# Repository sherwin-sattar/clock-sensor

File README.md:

# Clock-Sensor

## User Interface

Web user interface allows seamless control and customization of a clock display, featuring 86 addressable LEDs. Users can adjust and control the clock’s display from anywhere in the world through a secure online connection.
In addition to clock control, the UI also provides real-time monitoring of environmental conditions, including live temperature and humidity readings. Historical data is visualized through easy-to-read graphs, allowing users to track past temperature and humidity trends.

## 3D views

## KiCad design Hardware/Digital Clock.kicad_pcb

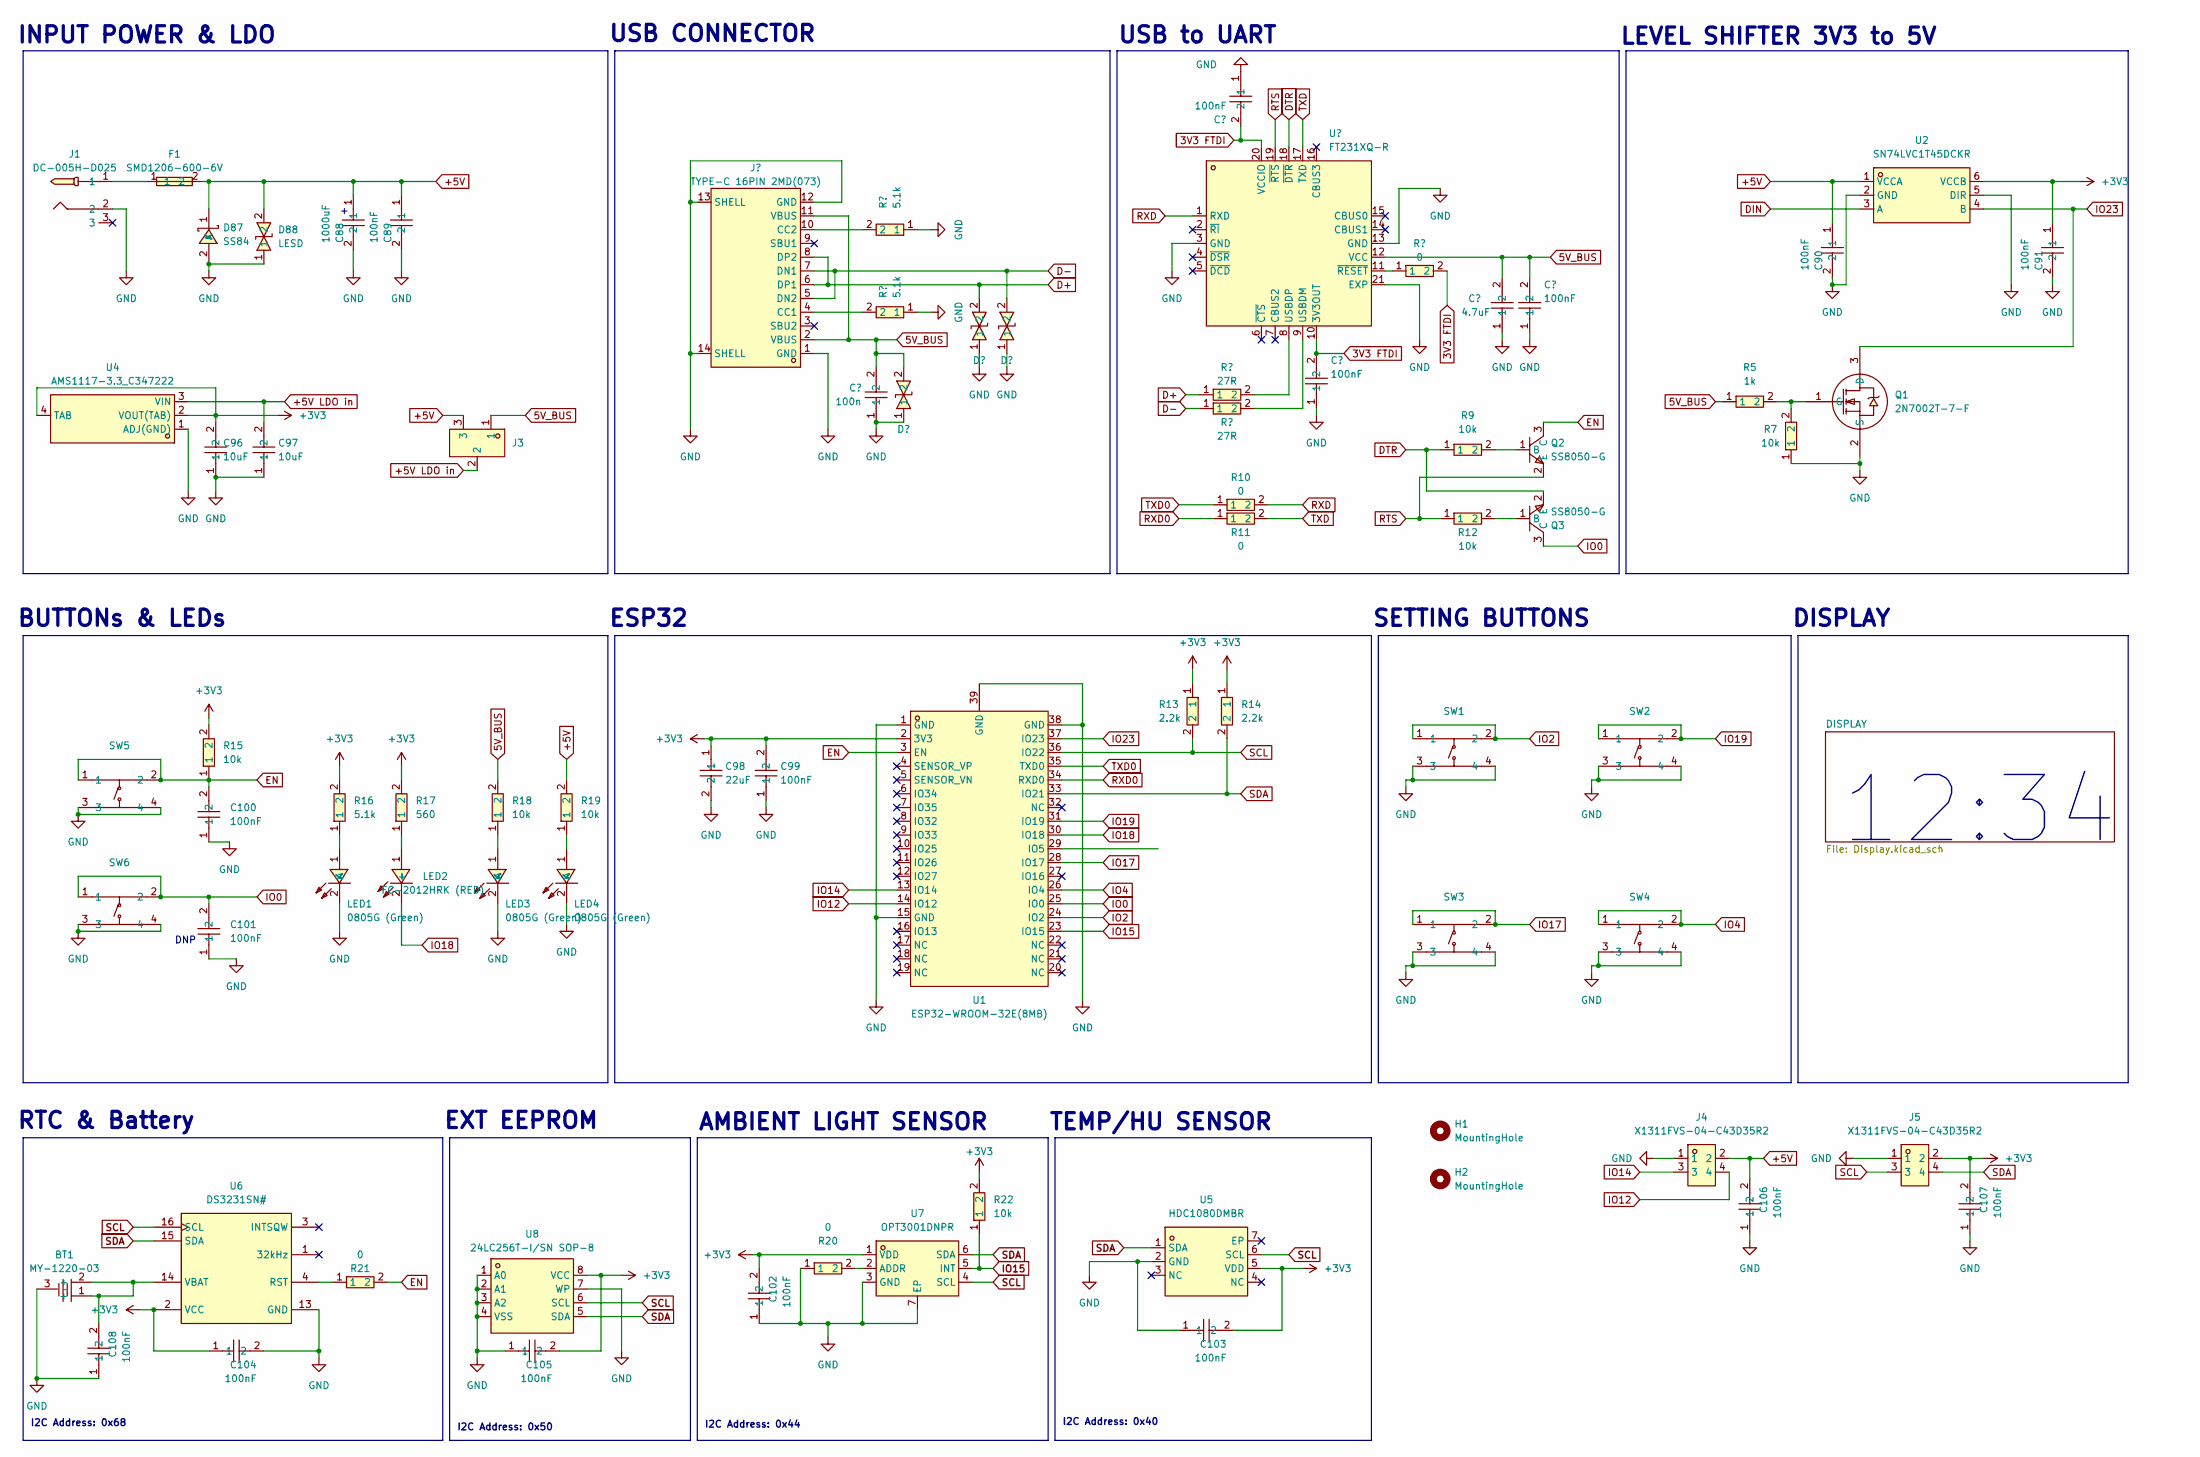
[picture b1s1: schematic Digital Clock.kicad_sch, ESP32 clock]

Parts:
BT1: MY-1220-03; BAT-SMD_MY-1220-03; LCSC Part C964818
C87, C89, C90, C91, C93, C94, C99, C100, C101, C102, C103, C104, C105, C106, C107, C108: 100nF; C0402; LCSC Part C1525
C88: 1000uF; CAP-SMD_BD10.0-L10.3-W10.3-LS11.3-FD; LCSC Part C310843
C92: 4.7uF; C0402; LCSC Part C368809
C95: 100n; C0402; LCSC Part C1525
C96, C97: 10uF; C0402; LCSC Part C315248
C98: 22uF; C0805; LCSC Part C602037
D87: SS84; SMC_L6.9-W5.9-LS7.9-RD; LCSC Part C2943761
D88: LESD; SOD-523_L1.2-W0.8-LS1.6-BI; LCSC Part C383211
D89, D90, D91: SOD-523_L1.2-W0.8-LS1.6-BI; LCSC Part C383211
F1: SMD1206-600-6V; F1206; LCSC Part C2760310
H1, H2: MountingHole; MountingHole_3.7mm_Pad_TopBottom
J1: DC-005H-D025; DC-IN-TH_G-SWITCH_DC-005H-D025; LCSC Part C5353839
J2: TYPE-C 16PIN 2MD(073); USB-C-SMD_TYPE-C-6PIN-2MD-073; LCSC Part C2765186
J3: X1311WVS-03J-C40D42R2; HDR-SMD_3P-P1.27-V-M-LS4.2_X1311WVS-03J-C40D42R2; LCSC Part C5243526
J4, J5: X1311FVS-04-C43D35R2; HDR-SMD_4P-P1.27-V-F-LS4.5_R2; LCSC Part C2881513
LED1, LED3, LED4: 0805G (Green); LED0805-R-RD; LCSC Part C2297
LED2: FC-2012HRK (RED); LED0805-R-RD; LCSC Part C84256
Q1: 2N7002T-7-F; SOT-523-3_L1.6-W0.8-P1.00-LS1.6-BR; LCSC Part C139445
Q2, Q3: SS8050-G; SOT-23-3_L2.9-W1.3-P1.90-LS2.4-BR; LCSC Part C164886
R2, R4, R16: 5.1k; R0402; LCSC Part C25905
R3, R10, R11, R20, R21: 0; R0402; LCSC Part C17168
R5: 1k; R0402; LCSC Part C11702
R6, R8: 27R; R0402; LCSC Part C138021
R7, R9, R12, R15, R18, R19, R22: 10k; R0402; LCSC Part C25744
R13, R14: 2.2k; R0402; LCSC Part C25879
R17: 560; R0402; LCSC Part C25126
SW1, SW2, SW3, SW4, SW5, SW6: PTS645SH50SMTR92LFS; KEY-SMD_4P-L6.0-W6.0-P4.50-LS9.0; LCSC Part C221869
U1: ESP32-WROOM-32E(8MB); WIFI-SMD_ESP32-WROOM-32E; LCSC Part C701342
U2: SN74LVC1T45DCKR; SC-70-6_L2.2-W1.3-P0.65-LS2.2-BR; LCSC Part C9382
U3: FT231XQ-R; QFN-20_L4.0-W4.0-P0.50-BL-EP2.2; LCSC Part C132159
U4: AMS1117-3.3_C347222; SOT-223-4_L6.5-W3.5-P2.30-LS7.0-BR; LCSC Part C347222
U5: HDC1080DMBR; SENSOR-SMD_HDC1080DMBR; LCSC Part C82227
U6: DS3231SN#; SOIC-16_L10.3-W7.5-P1.27-LS10.3-BL; LCSC Part C9866
U7: OPT3001DNPR; USON6_L2.1-W2.1-P0.65-BL-EP; LCSC Part C90462
U8: 24LC256T-I/SN SOP-8; SOIC-8_L4.9-W3.9-P1.27-LS6.0-BL; LCSC Part C5458

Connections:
3V3 FTDI: C87.2, C94.2, R3.2, U3.10 (3V3OUT), U3.20 (VCCIO)
5V_BUS: C92.2, C93.2, C95.2, D91.2, J2.2 (VBUS), J2.11 (VBUS), J3.1, R5.1, R18.2, U3.12 (VCC)
+3V3: C91.1, C96.2, C98.1, C99.2, C102.2, C103.2, C104.1, C105.2, C107.2, J5.2, R13.1, R14.1, R15.2, R16.2, R17.2, R22.2, U1.2 (3V3), U2.6 (VCCB), U4.2 (VOUT(TAB)), U4.4 (TAB), U5.5 (VDD), U6.2 (VCC), U7.1 (VDD), U8.8 (VCC)
+5V: C88.1, C89.1, C90.1, C106.2, D87.1 (K), D88.2, F1.2, J3.3, J4.2, R19.2, U2.1 (VCCA); also elsewhere on the board
+5V LDO in: C97.2, J3.2, U4.3 (VIN)
D+: D89.2, J2.6 (DP1), J2.8 (DP2), R6.1
D-: D90.2, J2.5 (DN2), J2.7 (DN1), R8.1
DIN: U2.3 (A); also elsewhere on the board
DTR: Q3.2 (E), R9.1, U3.18 (~DTR)
EN: C100.2, Q2.3 (C), R15.1, R21.2, SW5.1, SW5.2, U1.3 (EN)
GND: BT1.3 (-), C87.1, C88.2, C89.2, C90.2, C91.2, C92.1, C93.1, C94.1, C95.1, C96.1, C97.1, C98.2, C99.1, C100.1, C101.1, C102.1, C103.1, C104.2, C105.1, C106.1, C107.1, C108.1, D87.2 (A), D88.1, D89.1, D90.1, D91.1, J1.2, J2.1 (GND), J2.12 (GND), J2.13 (SHELL), J2.14 (SHELL), J4.1, J5.1, LED1.2 (K), LED3.2 (K), LED4.2 (K), Q1.2 (S), R2.1, R4.1, R7.1, R20.1, SW1.3, SW1.4, SW2.3, SW2.4, SW3.3, SW3.4, SW4.3, SW4.4, SW5.3, SW5.4, SW6.3, SW6.4, U1.1 (GND), U1.15 (GND), U1.38 (GND), U1.39 (GND), U2.2 (GND), U2.5 (DIR), U3.3 (GND), U3.13 (GND), U3.21 (EXP), U4.1 (ADJ(GND)), U5.2 (GND), U6.13 (GND), U7.3 (GND), U7.7 (EP), U8.1 (A0), U8.2 (A1), U8.3 (A2), U8.4 (VSS), U8.7 (WP); also elsewhere on the board
IO0: C101.2, Q3.3 (C), SW6.1, SW6.2, U1.25 (IO0)
IO2: SW1.1, SW1.2, U1.24 (IO2)
IO4: SW4.1, SW4.2, U1.26 (IO4)
IO12: J4.4, U1.14 (IO12)
IO14: J4.3, U1.13 (IO14)
IO15: R22.1, U1.23 (IO15), U7.5 (INT)
IO17: SW3.1, SW3.2, U1.28 (IO17)
IO18: LED2.2 (-), U1.30 (IO18); also elsewhere on the board
IO19: SW2.1, SW2.2, U1.31 (IO19)
IO23: Q1.3 (D), U1.37 (IO23), U2.4 (B)
unnamed: F1.1, J1.1
unnamed: J2.4 (CC1), R4.2
unnamed: J2.10 (CC2), R2.2
unnamed 102: LED1.1 (A), R16.1; also elsewhere on the board
unnamed 103: LED2.1 (+), R17.1; also elsewhere on the board
unnamed 104: LED3.1 (A), R18.1; also elsewhere on the board
unnamed 105: LED4.1 (A), R19.1; also elsewhere on the board
unnamed: Q1.1 (G), R5.2, R7.2
unnamed: Q2.1 (B), R9.2
unnamed: Q3.1 (B), R12.2
unnamed: R8.2, U3.9 (USBDM)
unnamed: R6.2, U3.8 (USBDP)
unnamed: R3.1, U3.11 (~RESET)
unnamed: R21.1, U6.4 (RST)
unnamed: BT1.1 (+), BT1.2 (+), C108.2, U6.14 (VBAT)
unnamed: R20.2, U7.2 (ADDR)
RTS: Q2.2 (E), R12.1, U3.19 (~RTS)
RXD: R10.2, U3.1 (RXD)
RXD0: R11.1, U1.34 (RXD0)
SCL: J5.3, R13.2, U1.36 (IO22), U5.6 (SCL), U6.16 (SCL), U7.4 (SCL), U8.6 (SCL)
SDA: J5.4, R14.2, U1.33 (IO21), U5.1 (SDA), U6.15 (SDA), U7.6 (SDA), U8.5 (SDA)
TXD: R11.2, U3.17 (TXD)
TXD0: R10.1, U1.35 (TXD0)

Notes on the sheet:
I2C Address: 0x44
INPUT POWER & LDO
USB CONNECTOR
BUTTONs & LEDs
USB to UART
ESP32
RTC & Battery
I2C Address: 0x68
EXT EEPROM
AMBIENT LIGHT SENSOR
I2C Address: 0x50
I2C Address: 0x40
DNP
TEMP/HU SENSOR
12:34
LEVEL SHIFTER 3V3 to 5V
SETTING BUTTONS
DISPLAY

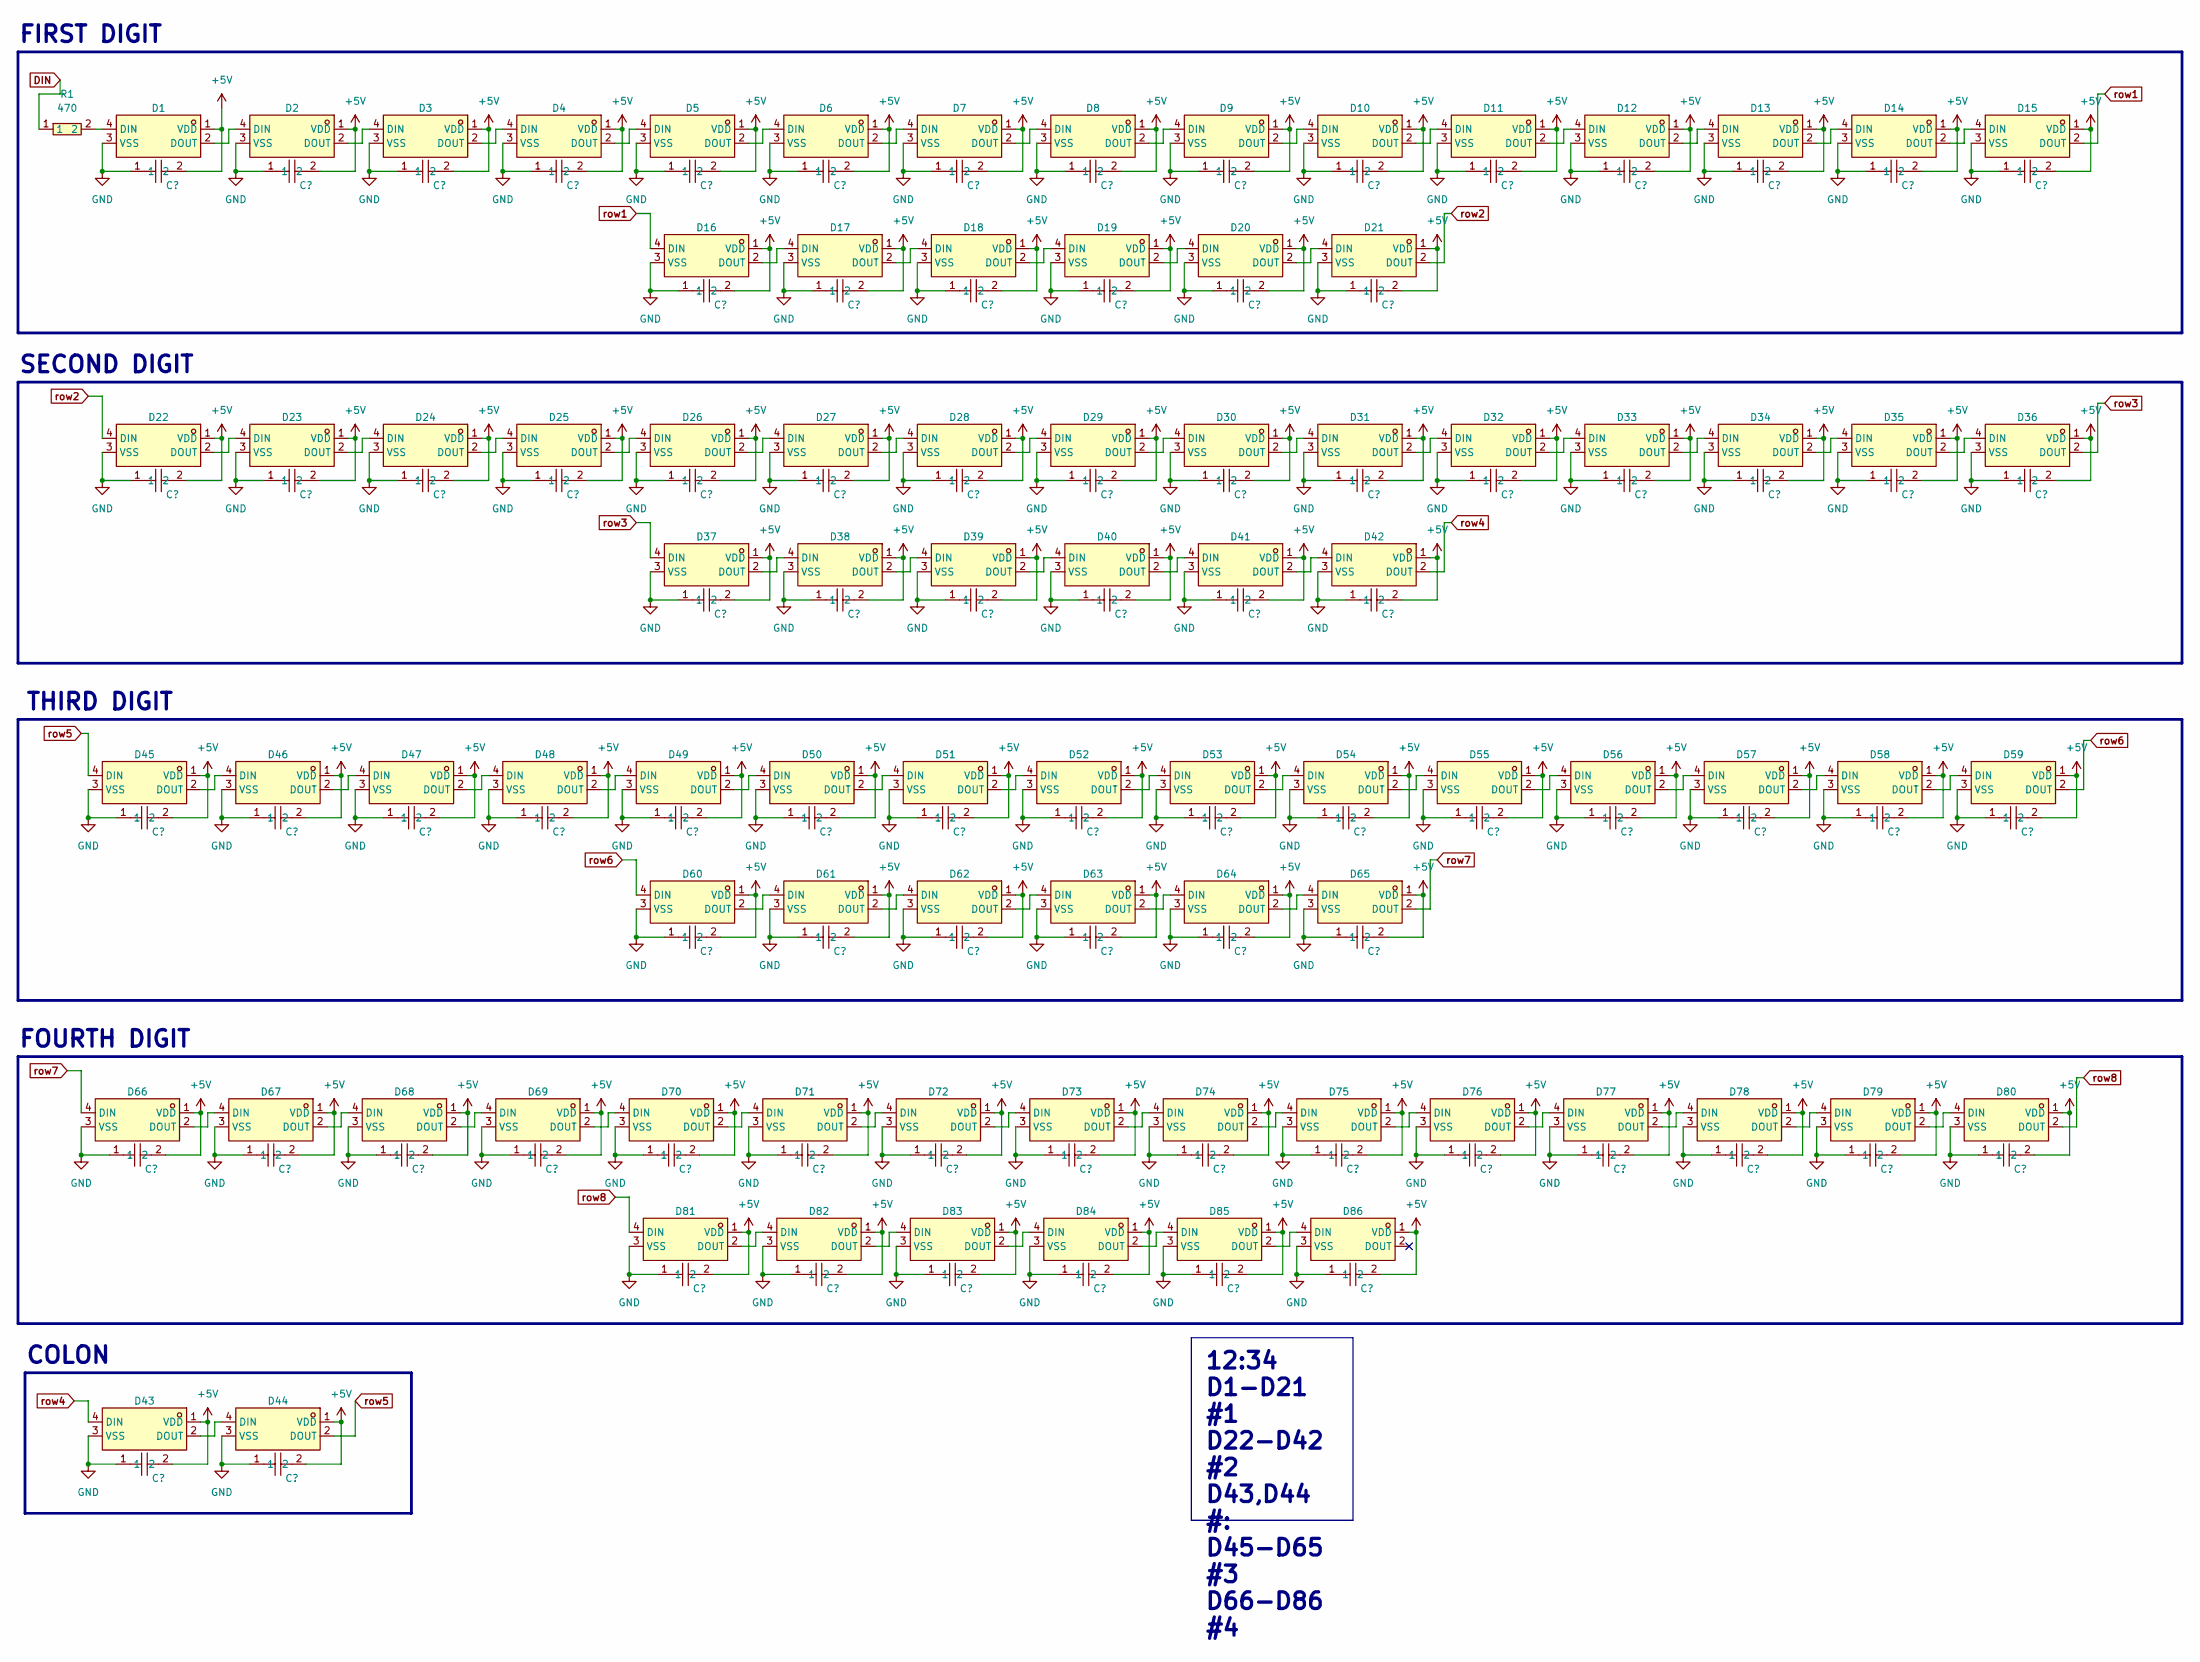
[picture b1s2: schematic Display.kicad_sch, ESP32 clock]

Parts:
C1, C2, C3, C4, C5, C6, C7, C8, C9, C10, C11, C12, C13, C14, C15, C16, C17, C18, C19, C20, C21, C22, C23, C24, C25, C26, C27, C28, C29, C30, C31, C32, C33, C34, C35, C36, C37, C38, C39, C40, C41, C42, C43, C44, C45, C46, C47, C48, C49, C50, C51, C52, C53, C54, C55, C56, C57, C58, C59, C60, C61, C62, C63, C64, C65, C66, C67, C68, C69, C70, C71, C72, C73, C74, C75, C76, C77, C78, C79, C80, C81, C82, C83, C84, C85, C86: 100nF; C0402; LCSC Part C1525
D1, D2, D3, D4, D5, D6, D7, D8, D9, D10, D11, D12, D13, D14, D15, D16, D17, D18, D19, D20, D21, D22, D23, D24, D25, D26, D27, D28, D29, D30, D31, D32, D33, D34, D35, D36, D37, D38, D39, D40, D41, D42, D43, D44, D45, D46, D47, D48, D49, D50, D51, D52, D53, D54, D55, D56, D57, D58, D59, D60, D61, D62, D63, D64, D65, D66, D67, D68, D69, D70, D71, D72, D73, D74, D75, D76, D77, D78, D79, D80, D81, D82, D83, D84, D85, D86: WS2812B-MINI; LED-SMD_4P-L3.5-W3.5-TL_WS2812B; LCSC Part C527089
R1: 470; R0402; LCSC Part C25117

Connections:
+5V: C1.2, C2.2, C3.2, C4.2, C5.2, C6.2, C7.2, C8.2, C9.2, C10.2, C11.2, C12.2, C13.2, C14.2, C15.2, C16.2, C17.2, C18.2, C19.2, C20.2, C21.2, C22.2, C23.2, C24.2, C25.2, C26.2, C27.2, C28.2, C29.2, C30.2, C31.2, C32.2, C33.2, C34.2, C35.2, C36.2, C37.2, C38.2, C39.2, C40.2, C41.2, C42.2, C43.2, C44.2, C45.2, C46.2, C47.2, C48.2, C49.2, C50.2, C51.2, C52.2, C53.2, C54.2, C55.2, C56.2, C57.2, C58.2, C59.2, C60.2, C61.2, C62.2, C63.2, C64.2, C65.2, C66.2, C67.2, C68.2, C69.2, C70.2, C71.2, C72.2, C73.2, C74.2, C75.2, C76.2, C77.2, C78.2, C79.2, C80.2, C81.2, C82.2, C83.2, C84.2, C85.2, C86.2, D1.1 (VDD), D2.1 (VDD), D3.1 (VDD), D4.1 (VDD), D5.1 (VDD), D6.1 (VDD), D7.1 (VDD), D8.1 (VDD), D9.1 (VDD), D10.1 (VDD), D11.1 (VDD), D12.1 (VDD), D13.1 (VDD), D14.1 (VDD), D15.1 (VDD), D16.1 (VDD), D17.1 (VDD), D18.1 (VDD), D19.1 (VDD), D20.1 (VDD), D21.1 (VDD), D22.1 (VDD), D23.1 (VDD), D24.1 (VDD), D25.1 (VDD), D26.1 (VDD), D27.1 (VDD), D28.1 (VDD), D29.1 (VDD), D30.1 (VDD), D31.1 (VDD), D32.1 (VDD), D33.1 (VDD), D34.1 (VDD), D35.1 (VDD), D36.1 (VDD), D37.1 (VDD), D38.1 (VDD), D39.1 (VDD), D40.1 (VDD), D41.1 (VDD), D42.1 (VDD), D43.1 (VDD), D44.1 (VDD), D45.1 (VDD), D46.1 (VDD), D47.1 (VDD), D48.1 (VDD), D49.1 (VDD), D50.1 (VDD), D51.1 (VDD), D52.1 (VDD), D53.1 (VDD), D54.1 (VDD), D55.1 (VDD), D56.1 (VDD), D57.1 (VDD), D58.1 (VDD), D59.1 (VDD), D60.1 (VDD), D61.1 (VDD), D62.1 (VDD), D63.1 (VDD), D64.1 (VDD), D65.1 (VDD), D66.1 (VDD), D67.1 (VDD), D68.1 (VDD), D69.1 (VDD), D70.1 (VDD), D71.1 (VDD), D72.1 (VDD), D73.1 (VDD), D74.1 (VDD), D75.1 (VDD), D76.1 (VDD), D77.1 (VDD), D78.1 (VDD), D79.1 (VDD), D80.1 (VDD), D81.1 (VDD), D82.1 (VDD), D83.1 (VDD), D84.1 (VDD), D85.1 (VDD), D86.1 (VDD); also elsewhere on the board
DIN: R1.1; also elsewhere on the board
GND: C1.1, C2.1, C3.1, C4.1, C5.1, C6.1, C7.1, C8.1, C9.1, C10.1, C11.1, C12.1, C13.1, C14.1, C15.1, C16.1, C17.1, C18.1, C19.1, C20.1, C21.1, C22.1, C23.1, C24.1, C25.1, C26.1, C27.1, C28.1, C29.1, C30.1, C31.1, C32.1, C33.1, C34.1, C35.1, C36.1, C37.1, C38.1, C39.1, C40.1, C41.1, C42.1, C43.1, C44.1, C45.1, C46.1, C47.1, C48.1, C49.1, C50.1, C51.1, C52.1, C53.1, C54.1, C55.1, C56.1, C57.1, C58.1, C59.1, C60.1, C61.1, C62.1, C63.1, C64.1, C65.1, C66.1, C67.1, C68.1, C69.1, C70.1, C71.1, C72.1, C73.1, C74.1, C75.1, C76.1, C77.1, C78.1, C79.1, C80.1, C81.1, C82.1, C83.1, C84.1, C85.1, C86.1, D1.3 (VSS), D2.3 (VSS), D3.3 (VSS), D4.3 (VSS), D5.3 (VSS), D6.3 (VSS), D7.3 (VSS), D8.3 (VSS), D9.3 (VSS), D10.3 (VSS), D11.3 (VSS), D12.3 (VSS), D13.3 (VSS), D14.3 (VSS), D15.3 (VSS), D16.3 (VSS), D17.3 (VSS), D18.3 (VSS), D19.3 (VSS), D20.3 (VSS), D21.3 (VSS), D22.3 (VSS), D23.3 (VSS), D24.3 (VSS), D25.3 (VSS), D26.3 (VSS), D27.3 (VSS), D28.3 (VSS), D29.3 (VSS), D30.3 (VSS), D31.3 (VSS), D32.3 (VSS), D33.3 (VSS), D34.3 (VSS), D35.3 (VSS), D36.3 (VSS), D37.3 (VSS), D38.3 (VSS), D39.3 (VSS), D40.3 (VSS), D41.3 (VSS), D42.3 (VSS), D43.3 (VSS), D44.3 (VSS), D45.3 (VSS), D46.3 (VSS), D47.3 (VSS), D48.3 (VSS), D49.3 (VSS), D50.3 (VSS), D51.3 (VSS), D52.3 (VSS), D53.3 (VSS), D54.3 (VSS), D55.3 (VSS), D56.3 (VSS), D57.3 (VSS), D58.3 (VSS), D59.3 (VSS), D60.3 (VSS), D61.3 (VSS), D62.3 (VSS), D63.3 (VSS), D64.3 (VSS), D65.3 (VSS), D66.3 (VSS), D67.3 (VSS), D68.3 (VSS), D69.3 (VSS), D70.3 (VSS), D71.3 (VSS), D72.3 (VSS), D73.3 (VSS), D74.3 (VSS), D75.3 (VSS), D76.3 (VSS), D77.3 (VSS), D78.3 (VSS), D79.3 (VSS), D80.3 (VSS), D81.3 (VSS), D82.3 (VSS), D83.3 (VSS), D84.3 (VSS), D85.3 (VSS), D86.3 (VSS); also elsewhere on the board
unnamed: D1.4 (DIN), R1.2
unnamed: D1.2 (DOUT), D2.4 (DIN)
unnamed: D2.2 (DOUT), D3.4 (DIN)
unnamed: D3.2 (DOUT), D4.4 (DIN)
unnamed: D4.2 (DOUT), D5.4 (DIN)
unnamed: D5.2 (DOUT), D6.4 (DIN)
unnamed: D6.2 (DOUT), D7.4 (DIN)
unnamed: D7.2 (DOUT), D8.4 (DIN)
unnamed: D8.2 (DOUT), D9.4 (DIN)
unnamed: D9.2 (DOUT), D10.4 (DIN)
unnamed: D10.2 (DOUT), D11.4 (DIN)
unnamed: D11.2 (DOUT), D12.4 (DIN)
unnamed: D12.2 (DOUT), D13.4 (DIN)
unnamed: D13.2 (DOUT), D14.4 (DIN)
unnamed: D14.2 (DOUT), D15.4 (DIN)
unnamed: D16.2 (DOUT), D17.4 (DIN)
unnamed: D17.2 (DOUT), D18.4 (DIN)
unnamed: D18.2 (DOUT), D19.4 (DIN)
unnamed: D19.2 (DOUT), D20.4 (DIN)
unnamed: D20.2 (DOUT), D21.4 (DIN)
unnamed: D22.2 (DOUT), D23.4 (DIN)
unnamed: D23.2 (DOUT), D24.4 (DIN)
unnamed: D24.2 (DOUT), D25.4 (DIN)
unnamed: D25.2 (DOUT), D26.4 (DIN)
unnamed: D26.2 (DOUT), D27.4 (DIN)
unnamed: D27.2 (DOUT), D28.4 (DIN)
unnamed: D28.2 (DOUT), D29.4 (DIN)
unnamed: D29.2 (DOUT), D30.4 (DIN)
unnamed: D30.2 (DOUT), D31.4 (DIN)
unnamed: D31.2 (DOUT), D32.4 (DIN)
unnamed: D32.2 (DOUT), D33.4 (DIN)
unnamed: D33.2 (DOUT), D34.4 (DIN)
unnamed: D34.2 (DOUT), D35.4 (DIN)
unnamed: D35.2 (DOUT), D36.4 (DIN)
unnamed: D37.2 (DOUT), D38.4 (DIN)
unnamed: D38.2 (DOUT), D39.4 (DIN)
unnamed: D39.2 (DOUT), D40.4 (DIN)
unnamed: D40.2 (DOUT), D41.4 (DIN)
unnamed: D41.2 (DOUT), D42.4 (DIN)
unnamed: D43.2 (DOUT), D44.4 (DIN)
unnamed: D45.2 (DOUT), D46.4 (DIN)
unnamed: D46.2 (DOUT), D47.4 (DIN)
unnamed: D47.2 (DOUT), D48.4 (DIN)
unnamed: D48.2 (DOUT), D49.4 (DIN)
unnamed: D49.2 (DOUT), D50.4 (DIN)
unnamed: D50.2 (DOUT), D51.4 (DIN)
unnamed: D51.2 (DOUT), D52.4 (DIN)
unnamed: D52.2 (DOUT), D53.4 (DIN)
unnamed: D53.2 (DOUT), D54.4 (DIN)
unnamed: D54.2 (DOUT), D55.4 (DIN)
unnamed: D55.2 (DOUT), D56.4 (DIN)
unnamed: D56.2 (DOUT), D57.4 (DIN)
unnamed: D57.2 (DOUT), D58.4 (DIN)
unnamed: D58.2 (DOUT), D59.4 (DIN)
unnamed: D60.2 (DOUT), D61.4 (DIN)
unnamed: D61.2 (DOUT), D62.4 (DIN)
unnamed: D62.2 (DOUT), D63.4 (DIN)
unnamed: D63.2 (DOUT), D64.4 (DIN)
unnamed: D64.2 (DOUT), D65.4 (DIN)
unnamed: D66.2 (DOUT), D67.4 (DIN)
unnamed: D67.2 (DOUT), D68.4 (DIN)
unnamed: D68.2 (DOUT), D69.4 (DIN)
unnamed: D69.2 (DOUT), D70.4 (DIN)
unnamed: D70.2 (DOUT), D71.4 (DIN)
unnamed: D71.2 (DOUT), D72.4 (DIN)
unnamed: D72.2 (DOUT), D73.4 (DIN)
unnamed: D73.2 (DOUT), D74.4 (DIN)
unnamed: D74.2 (DOUT), D75.4 (DIN)
unnamed: D75.2 (DOUT), D76.4 (DIN)
unnamed: D76.2 (DOUT), D77.4 (DIN)
unnamed: D77.2 (DOUT), D78.4 (DIN)
unnamed: D78.2 (DOUT), D79.4 (DIN)
unnamed: D79.2 (DOUT), D80.4 (DIN)
unnamed: D81.2 (DOUT), D82.4 (DIN)
unnamed: D82.2 (DOUT), D83.4 (DIN)
unnamed: D83.2 (DOUT), D84.4 (DIN)
unnamed: D84.2 (DOUT), D85.4 (DIN)
unnamed: D85.2 (DOUT), D86.4 (DIN)
row1: D15.2 (DOUT), D16.4 (DIN)
row2: D21.2 (DOUT), D22.4 (DIN)
row3: D36.2 (DOUT), D37.4 (DIN)
row4: D42.2 (DOUT), D43.4 (DIN)
row5: D44.2 (DOUT), D45.4 (DIN)
row6: D59.2 (DOUT), D60.4 (DIN)
row7: D65.2 (DOUT), D66.4 (DIN)
row8: D80.2 (DOUT), D81.4 (DIN)

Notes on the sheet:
12:34 D1-D21 #1 D22-D42 #2 D43,D44 #: D45-D65 #3 D66-D86 #4
FOURTH DIGIT
SECOND DIGIT
COLON
FIRST DIGIT
THIRD DIGIT

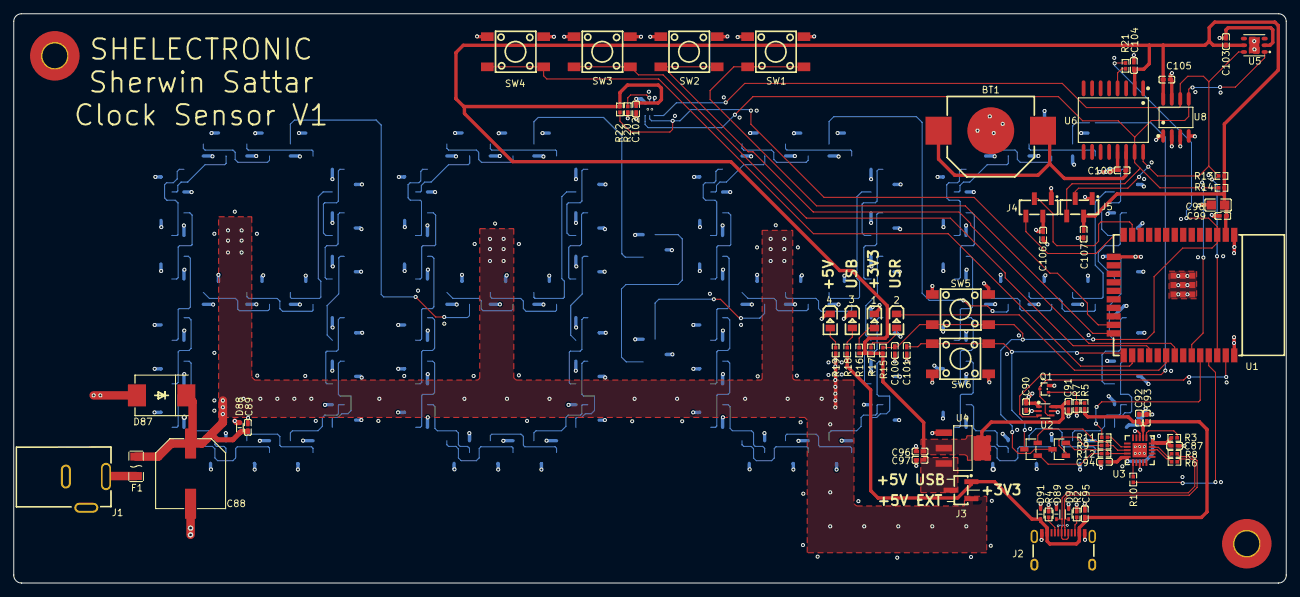
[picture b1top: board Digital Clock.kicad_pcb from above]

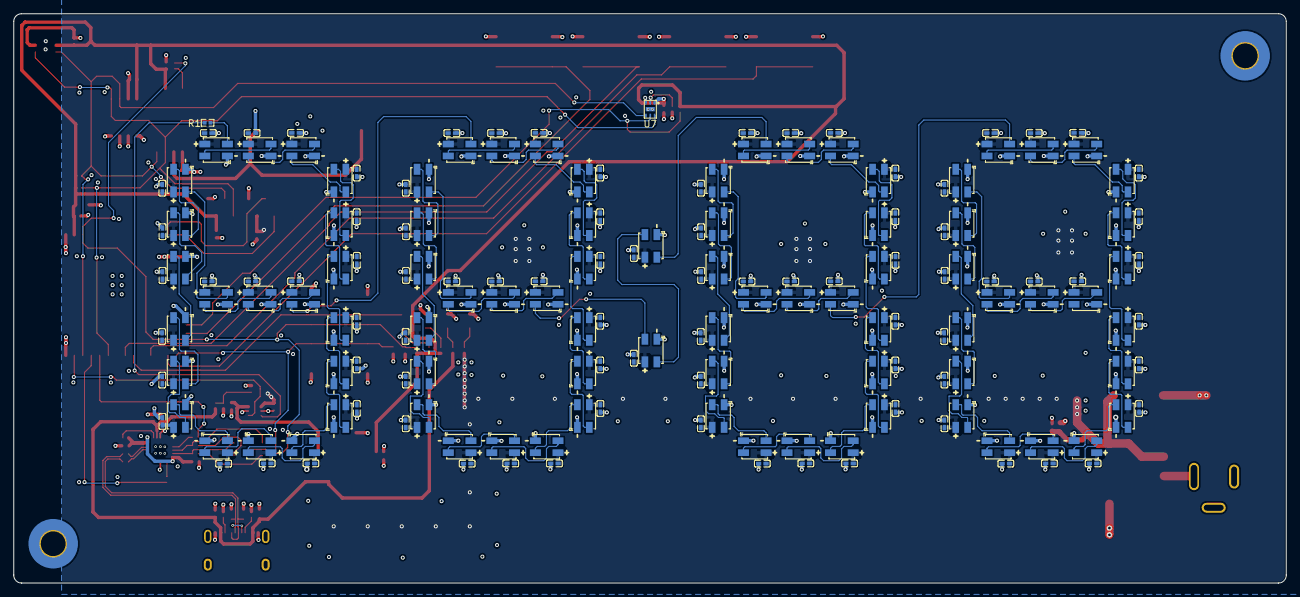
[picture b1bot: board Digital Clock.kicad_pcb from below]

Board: 4 copper layers, 190.0 x 85.0 mm, 251 parts (174 on the bottom side), 130 nets.

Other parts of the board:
1, 3, 4: 0805G (Green); LED0805-R-RD
2: FC-2012HRK (RED); LED0805-R-RD

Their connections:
GND: 1.2 (K), 3.2 (K), 4.2 (K); also elsewhere on the board
IO18: 2.2 (-); also elsewhere on the board
unnamed 102: 1.1 (A); also elsewhere on the board
unnamed 103: 2.1 (+); also elsewhere on the board
unnamed 104: 3.1 (A); also elsewhere on the board
unnamed 105: 4.1 (A); also elsewhere on the board
